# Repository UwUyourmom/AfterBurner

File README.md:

## AfterBurner

This is my backup/posting of my little Afterburner test piece, \
Its not great but i have seen worse
# Testing vid on my youtube [AfterburnerTest](https://youtu.be/r_q5uBkwENI?si=lZsYyg5NFj2jl1zo)
Also some pics

I have used the following Materials: 
|          | Steeltube | Acrylictube |  
|----------|----------|----------|
| Outer Diameter   | 6cm  | 6.5cm |
| Length    | 16cm  | 29cm  |
| thickness    |  2.75mm  | 3.6mm  |

The Stl files for the pipeclamps etc are all in the [Stl folder](https://github.com/UwUyourmom/AfterBurner/tree/main/STL) \
The PCB files are there but since i have <mark>NOT</mark> tested them yet i wont link it\
But Renders of the PCB fine trust:\

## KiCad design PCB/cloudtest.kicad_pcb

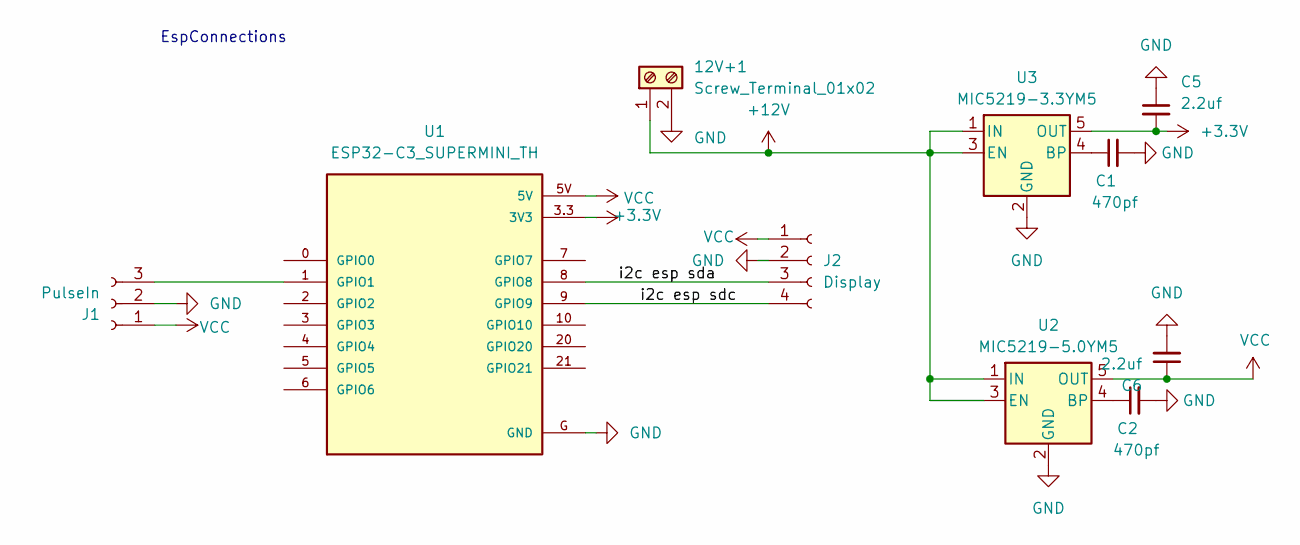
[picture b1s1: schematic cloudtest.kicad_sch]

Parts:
12V+1: Screw_Terminal_01x02; TerminalBlock_bornier-2_P5.08mm
C1, C2: 470pf; C_Disc_D5.0mm_W2.5mm_P5.00mm
C5, C6: 2.2uf; CP_Radial_D5.0mm_P2.50mm
J1: PulseIn; PinHeader_1x03_P1.27mm_Vertical
J2: Display; PinHeader_1x04_P1.27mm_Vertical
U1: ESP32-C3_SUPERMINI_TH; MODULE_ESP32-C3_SUPERMINI
U2: MIC5219-5.0YM5; SOT-23-5
U3: MIC5219-3.3YM5; SOT-23-5

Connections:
+3.3V: C5.2, U1.3.3 (3V3), U3.5 (OUT)
+12V: 12V+1.1, U2.1 (IN), U2.3 (EN), U3.1 (IN), U3.3 (EN)
/i2c esp sda: J2.3, U1.8 (GPIO8)
/i2c esp sdc: J2.4, U1.9 (GPIO9)
GND: 12V+1.2, C1.2, C2.2, C5.1, C6.2, J1.2, J2.2, U1.G (GND), U2.2 (GND), U3.2 (GND)
unnamed: J1.3, U1.1 (GPIO1)
unnamed: C2.1, U2.4 (BP)
unnamed: C1.1, U3.4 (BP)
VCC: C6.1, J1.1, J2.1, U1.5V, U2.5 (OUT)

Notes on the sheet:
EspConnections

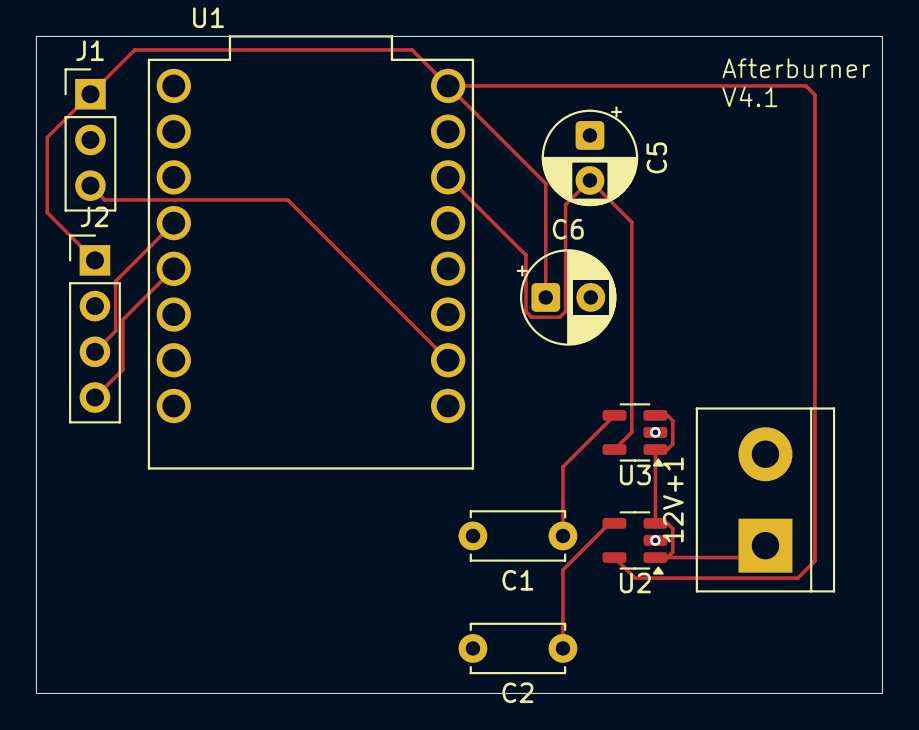
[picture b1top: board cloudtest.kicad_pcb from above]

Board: 2 copper layers, 47.0 x 36.5 mm, 10 parts (0 on the bottom side), 9 nets.

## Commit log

2025-02-22 Connector for acrylic tube and steal tube
2025-02-22 Change in folder structure
2025-02-22 futher stuff
2025-03-05 dings
2025-04-06 Code for Esp32 -c3 supermini
    not really working till now
2025-04-06 Create test
2025-04-06 upload pic for readme
2025-04-07 Rename ConnectorBetter v3.stl to Connector v3.stl
2025-04-07 Rename HalterRohr v3.stl to HolderMetallPipe v3.stl
2025-04-07 Rename Halterung rohr v2.stl to HolderAcrylicTubev2.stl
2025-04-07 finally reads out the right value
2025-04-07 Update README.md(work in progress)
2025-06-08 Transpiled mainframe.
2025-06-08 Adding the pcb files (Pcb still in testing
2025-06-27 Add pic of pcb render
2025-07-20 Fixed PCB (hopefully)
